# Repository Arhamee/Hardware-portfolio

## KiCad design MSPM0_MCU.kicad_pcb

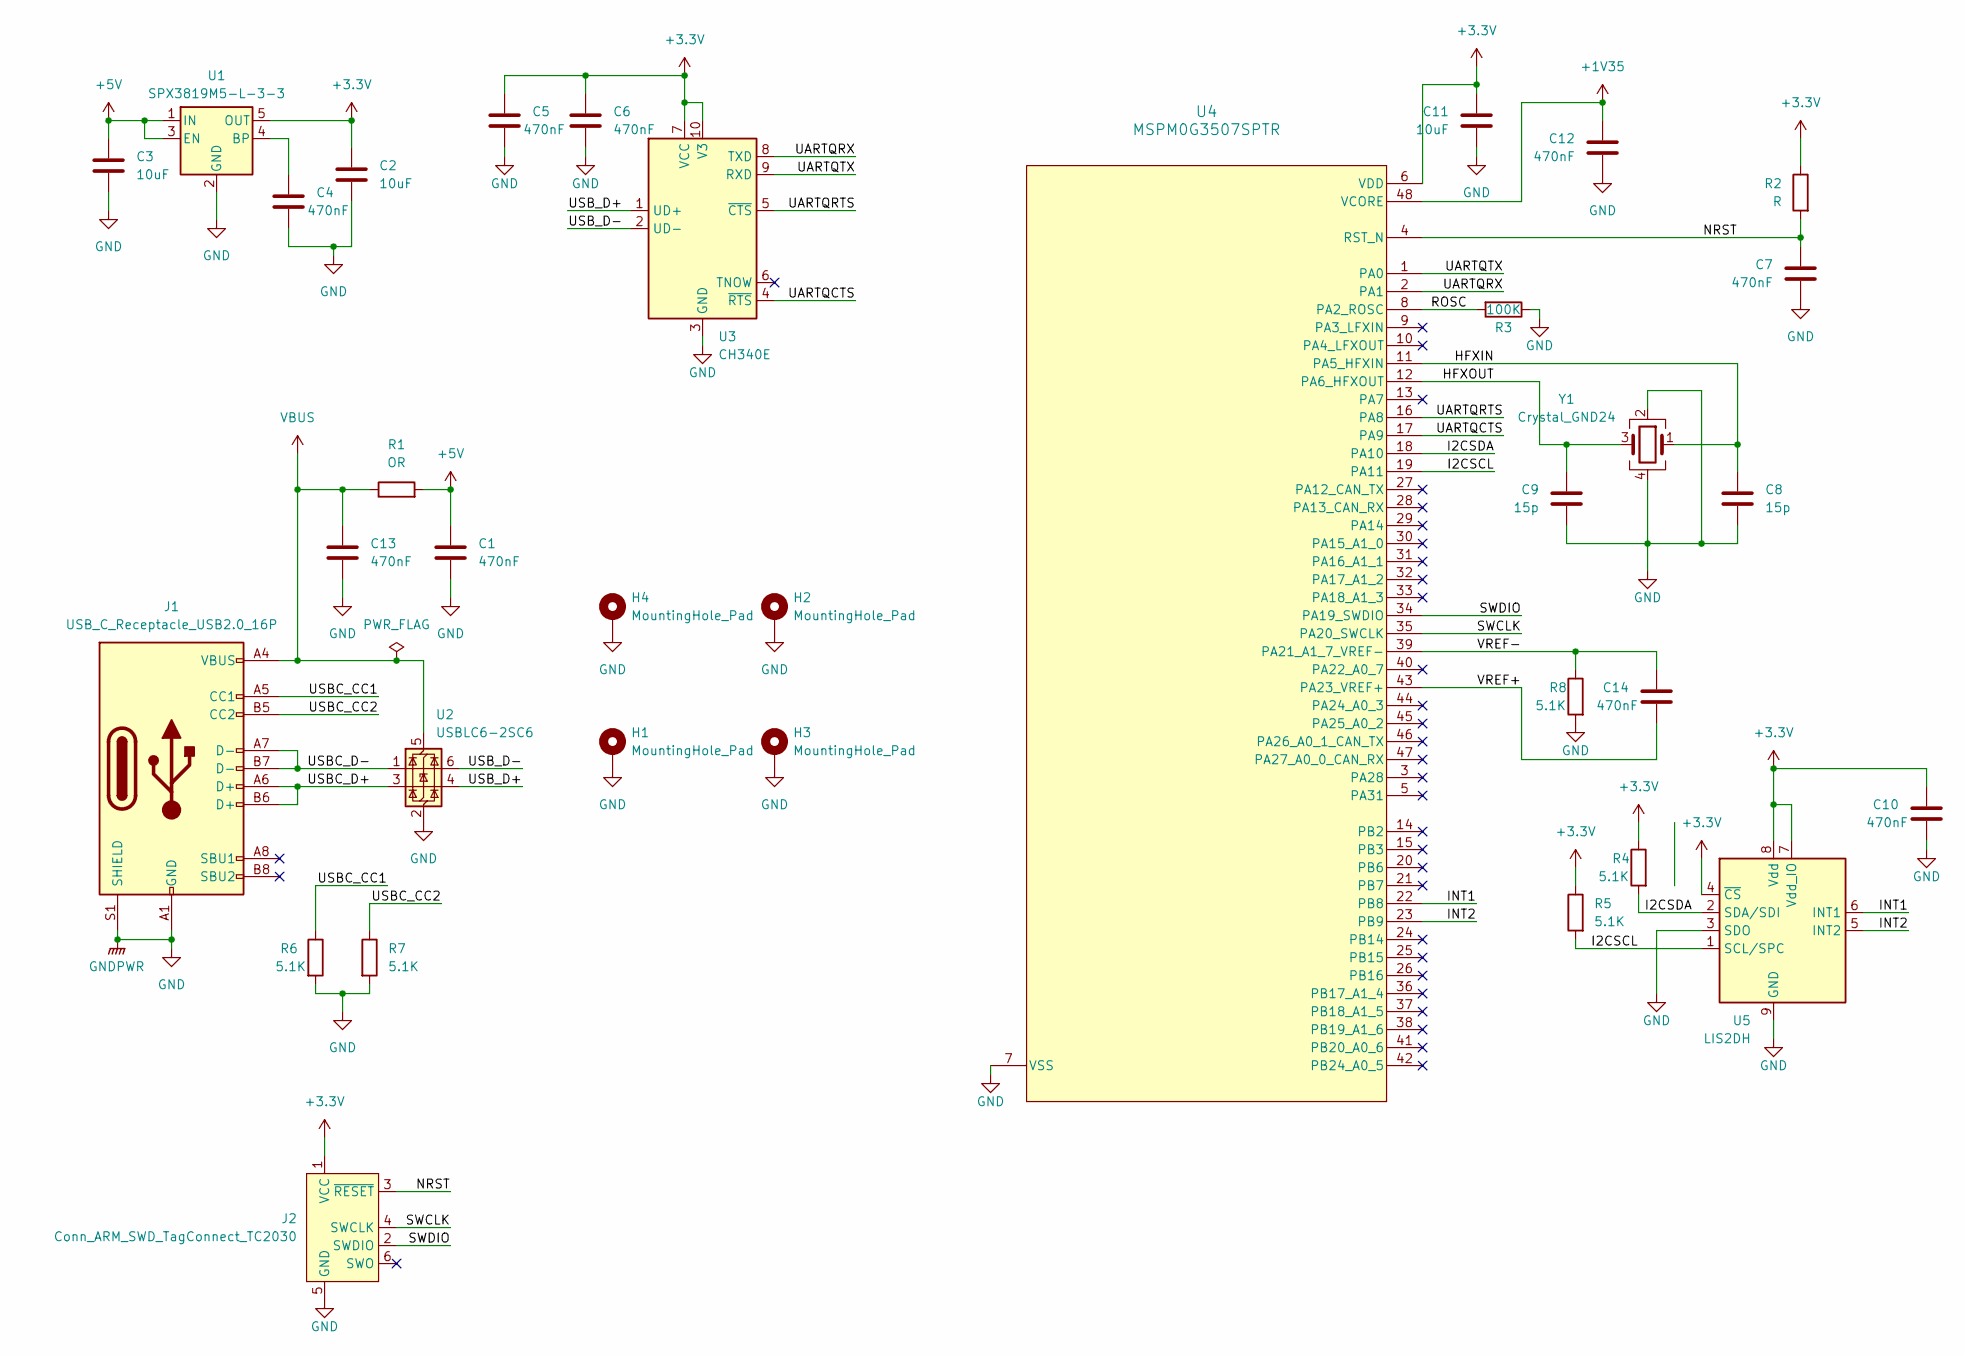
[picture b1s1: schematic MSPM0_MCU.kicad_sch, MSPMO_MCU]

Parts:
C1, C4, C5, C6, C7, C10, C12, C13, C14: 470nF; C_0603_1608Metric_Pad1.08x0.95mm_HandSolder
C2, C3, C11: 10uF; C_0805_2012Metric_Pad1.18x1.45mm_HandSolder
C8, C9: 15p; C_0603_1608Metric_Pad1.08x0.95mm_HandSolder
H1, H2, H3, H4: MountingHole_Pad; MountingHole_3.2mm_M3_Pad_Via
J1: USB_C_Receptacle_USB2.0_16P; USB_C_Receptacle_GCT_USB4105-xx-A_16P_TopMnt_Horizontal
J2: Conn_ARM_SWD_TagConnect_TC2030; Tag-Connect_TC2030-IDC-FP_2x03_P1.27mm_Vertical
R1: OR; R_0603_1608Metric_Pad0.98x0.95mm_HandSolder
R2: R; R_0603_1608Metric_Pad0.98x0.95mm_HandSolder
R3: 100K; R_0603_1608Metric_Pad0.98x0.95mm_HandSolder
R4, R5, R6, R7, R8: 5.1K; R_0603_1608Metric_Pad0.98x0.95mm_HandSolder
U1: SPX3819M5-L-3-3; SOT-23-5
U2: USBLC6-2SC6; SOT-23-6
U3: CH340E; MSOP-10_3x3mm_P0.5mm
U4: MSPM0G3507SPTR; PT0048A-IPC_A
U5: LIS2DH; LGA-14_2x2mm_P0.35mm_LayoutBorder3x4y
Y1: Crystal_GND24; Crystal_SMD_3225-4Pin_3.2x2.5mm_HandSoldering

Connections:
+1V35: C12.1, U4.48 (VCORE)
+3.3V: C2.1, C5.1, C6.1, C10.1, C11.1, J2.1 (VCC), R2.1, R4.1, R5.1, U1.5 (OUT), U3.7 (VCC), U3.10 (V3), U4.6 (VDD), U5.4 (~CS), U5.7 (Vdd_IO), U5.8 (Vdd)
+5V: C1.1, C3.1, R1.2, U1.1 (IN), U1.3 (EN)
/HFXIN: C8.1, U4.11 (PA5_HFXIN), Y1.1
/HFXOUT: C9.1, U4.12 (PA6_HFXOUT), Y1.3
/I2CSCL: R5.2, U4.19 (PA11), U5.1 (SCL/SPC)
/I2CSDA: R4.2, U4.18 (PA10), U5.2 (SDA/SDI)
/INT1: U4.22 (PB8), U5.6 (INT1)
/INT2: U4.23 (PB9), U5.5 (INT2)
/NRST: C7.1, J2.3 (~RESET), R2.2, U4.4 (RST_N)
/ROSC: R3.2, U4.8 (PA2_ROSC)
/SWCLK: J2.4 (SWCLK), U4.35 (PA20_SWCLK)
/SWDIO: J2.2 (SWDIO), U4.34 (PA19_SWDIO)
/UARTQCTS: U3.4 (~RTS), U4.17 (PA9)
/UARTQRTS: U3.5 (~CTS), U4.16 (PA8)
/UARTQRX: U3.8 (TXD), U4.2 (PA1)
/UARTQTX: U3.9 (RXD), U4.1 (PA0)
/USBC_CC1: J1.A5 (CC1), R6.1
/USBC_CC2: J1.B5 (CC2), R7.1
/USBC_D+: J1.A6 (D+), J1.B6 (D+), U2.3 (I/O2)
/USBC_D-: J1.A7 (D-), J1.B7 (D-), U2.1 (I/O1)
/USB_D+: U2.4 (I/O2), U3.1 (UD+)
/USB_D-: U2.6 (I/O1), U3.2 (UD-)
/VREF+: C14.2, U4.43 (PA23_VREF+)
/VREF-: C14.1, R8.1, U4.39 (PA21_A1_7_VREF-)
GND: C1.2, C2.2, C3.2, C4.2, C5.2, C6.2, C7.2, C8.2, C9.2, C10.2, C11.2, C12.2, C13.2, H1.1, H2.1, H3.1, H4.1, J1.A1 (GND), J1.A12 (GND), J1.B1 (GND), J1.B12 (GND), J1.S1 (SHIELD), J2.5 (GND), R3.1, R6.2, R7.2, R8.2, U1.2 (GND), U2.2 (GND), U3.3 (GND), U4.7 (VSS), U5.3 (SDO), U5.9 (GND), U5.10 (GND), U5.11 (GND), U5.12 (GND), U5.13 (GND), U5.14 (GND), Y1.2, Y1.4
unnamed: C4.1, U1.4 (BP)
VBUS: C13.1, J1.A4 (VBUS), J1.A9 (VBUS), J1.B4 (VBUS), J1.B9 (VBUS), R1.1, U2.5 (VBUS)

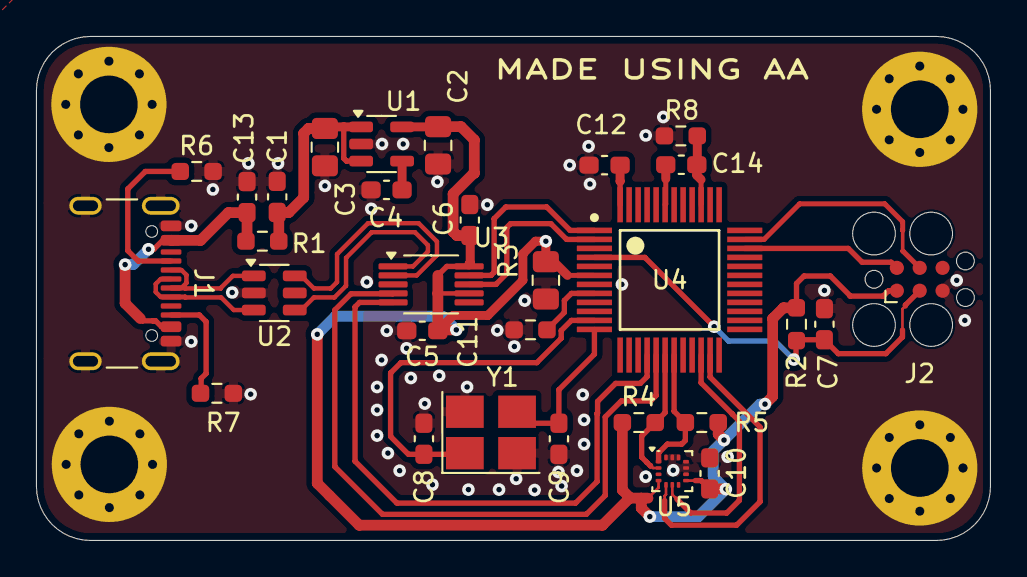
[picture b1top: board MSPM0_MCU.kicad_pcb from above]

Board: 2 copper layers, 53.0 x 28.0 mm, 34 parts (0 on the bottom side), 28 nets.

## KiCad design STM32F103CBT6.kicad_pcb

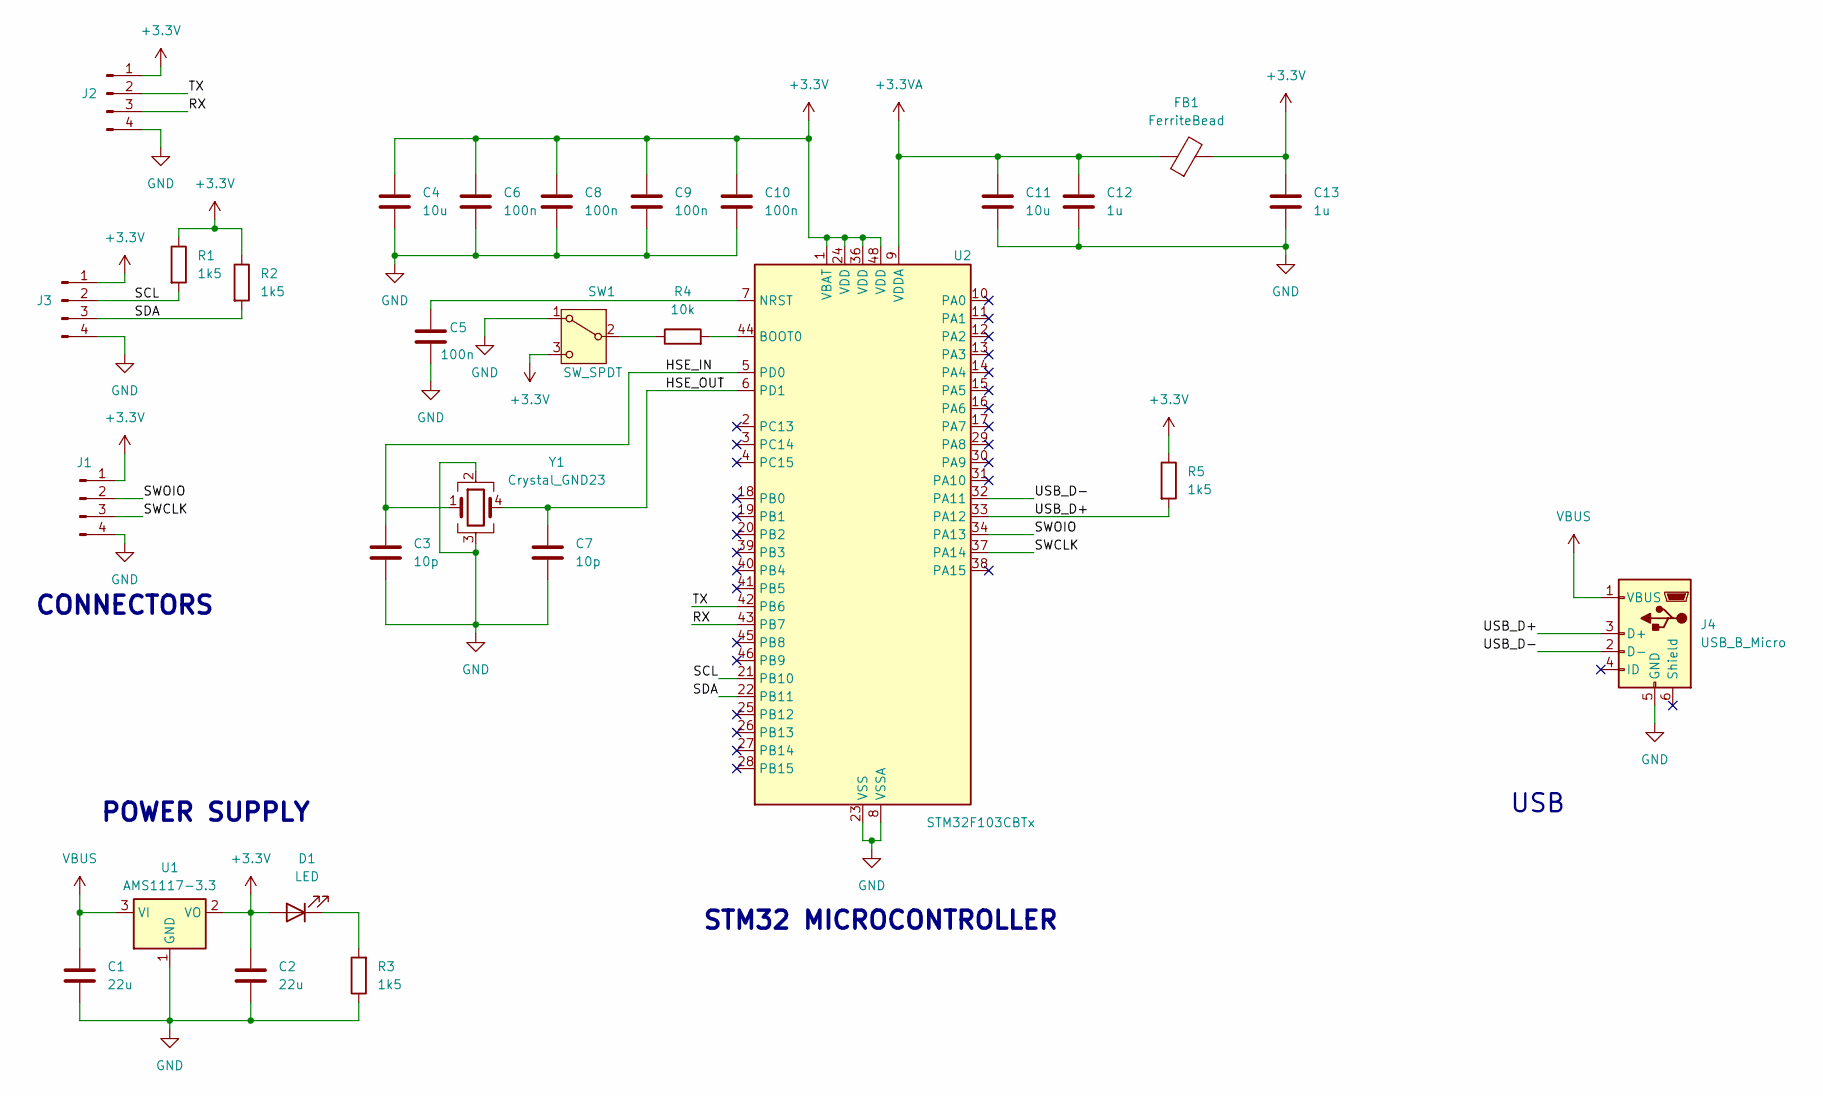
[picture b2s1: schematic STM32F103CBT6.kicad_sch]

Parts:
C1, C2: 22u; C_0805_2012Metric_Pad1.18x1.45mm_HandSolder
C3, C7: 10p; C_0402_1005Metric_Pad0.74x0.62mm_HandSolder
C4: 10u; C_0402_1005Metric_Pad0.74x0.62mm_HandSolder
C5, C6, C8, C9, C10: 100n; C_0402_1005Metric_Pad0.74x0.62mm_HandSolder
C11: 10u; C_0603_1608Metric_Pad1.08x0.95mm_HandSolder
C12, C13: 1u; C_0402_1005Metric_Pad0.74x0.62mm_HandSolder
D1: LED; LED_0201_0603Metric_Pad0.64x0.40mm_HandSolder
FB1: FerriteBead; L_0201_0603Metric_Pad0.64x0.40mm_HandSolder
J1, J2, J3: Conn_01x04_Pin; PinHeader_1x04_P2.54mm_Vertical
J4: USB_B_Micro; USB_Micro-B_Wuerth_629105150521
R1, R2, R3, R5: 1k5; R_0402_1005Metric_Pad0.72x0.64mm_HandSolder
R4: 10k; R_0402_1005Metric_Pad0.72x0.64mm_HandSolder
SW1: SW_SPDT; SW_Slide-03_Wuerth-WS-SLTV_10x2.5x6.4_P2.54mm
U1: AMS1117-3.3; SOT-223-3_TabPin2
U2: STM32F103CBTx; LQFP-48_7x7mm_P0.5mm
Y1: Crystal_GND23; Crystal_SMD_3225-4Pin_3.2x2.5mm

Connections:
+3.3V: C2.1, C4.1, C6.1, C8.1, C9.1, C10.1, C13.1, D1.2 (A), FB1.2, J1.1, J2.1, J3.1, R1.1, R2.1, R5.1, SW1.3 (C), U1.2 (VO), U2.1 (VBAT), U2.24 (VDD), U2.36 (VDD), U2.48 (VDD)
+3.3VA: C11.1, C12.1, FB1.1, U2.9 (VDDA)
/HSE_IN: C3.1, U2.5 (PD0), Y1.1
/HSE_OUT: C7.1, U2.6 (PD1), Y1.4
/RX: J2.3, U2.43 (PB7)
/SCL: J3.2, R1.2, U2.21 (PB10)
/SDA: J3.3, R2.2, U2.22 (PB11)
/SWCLK: J1.3, U2.37 (PA14)
/SWOIO: J1.2, U2.34 (PA13)
/TX: J2.2, U2.42 (PB6)
/USB_D+: J4.3 (D+), R5.2, U2.33 (PA12)
/USB_D-: J4.2 (D-), U2.32 (PA11)
GND: C1.2, C2.2, C3.2, C4.2, C5.2, C6.2, C7.2, C8.2, C9.2, C10.2, C11.2, C12.2, C13.2, J1.4, J2.4, J3.4, J4.5 (GND), R3.1, SW1.1 (A), U1.1 (GND), U2.8 (VSSA), U2.23 (VSS), U2.35 (VSS), U2.47 (VSS), Y1.2, Y1.3
unnamed: D1.1 (K), R3.2
unnamed: R4.1, SW1.2 (B)
unnamed: R4.2, U2.44 (BOOT0)
unnamed: C5.1, U2.7 (NRST)
VBUS: C1.1, J4.1 (VBUS), U1.3 (VI)

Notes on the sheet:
POWER SUPPLY
STM32 MICROCONTROLLER
CONNECTORS
USB

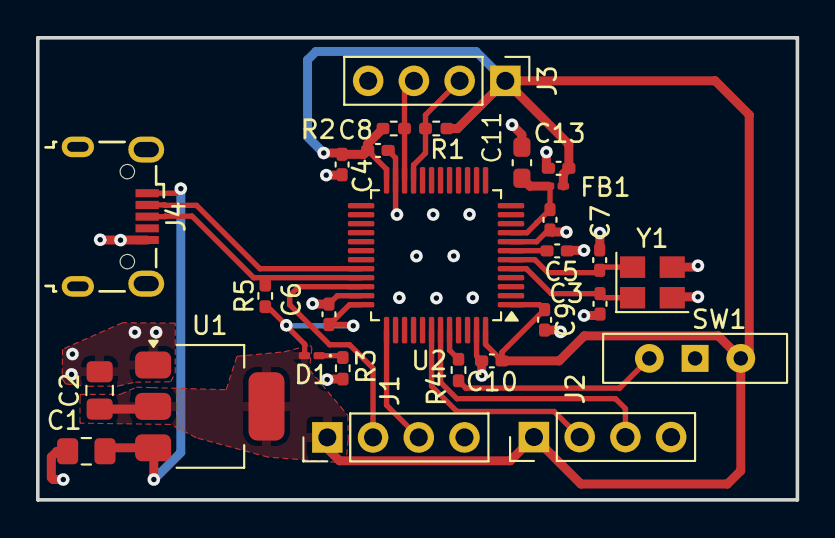
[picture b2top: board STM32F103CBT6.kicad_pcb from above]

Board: 2 copper layers, 42.2 x 25.7 mm, 28 parts (0 on the bottom side), 18 nets.

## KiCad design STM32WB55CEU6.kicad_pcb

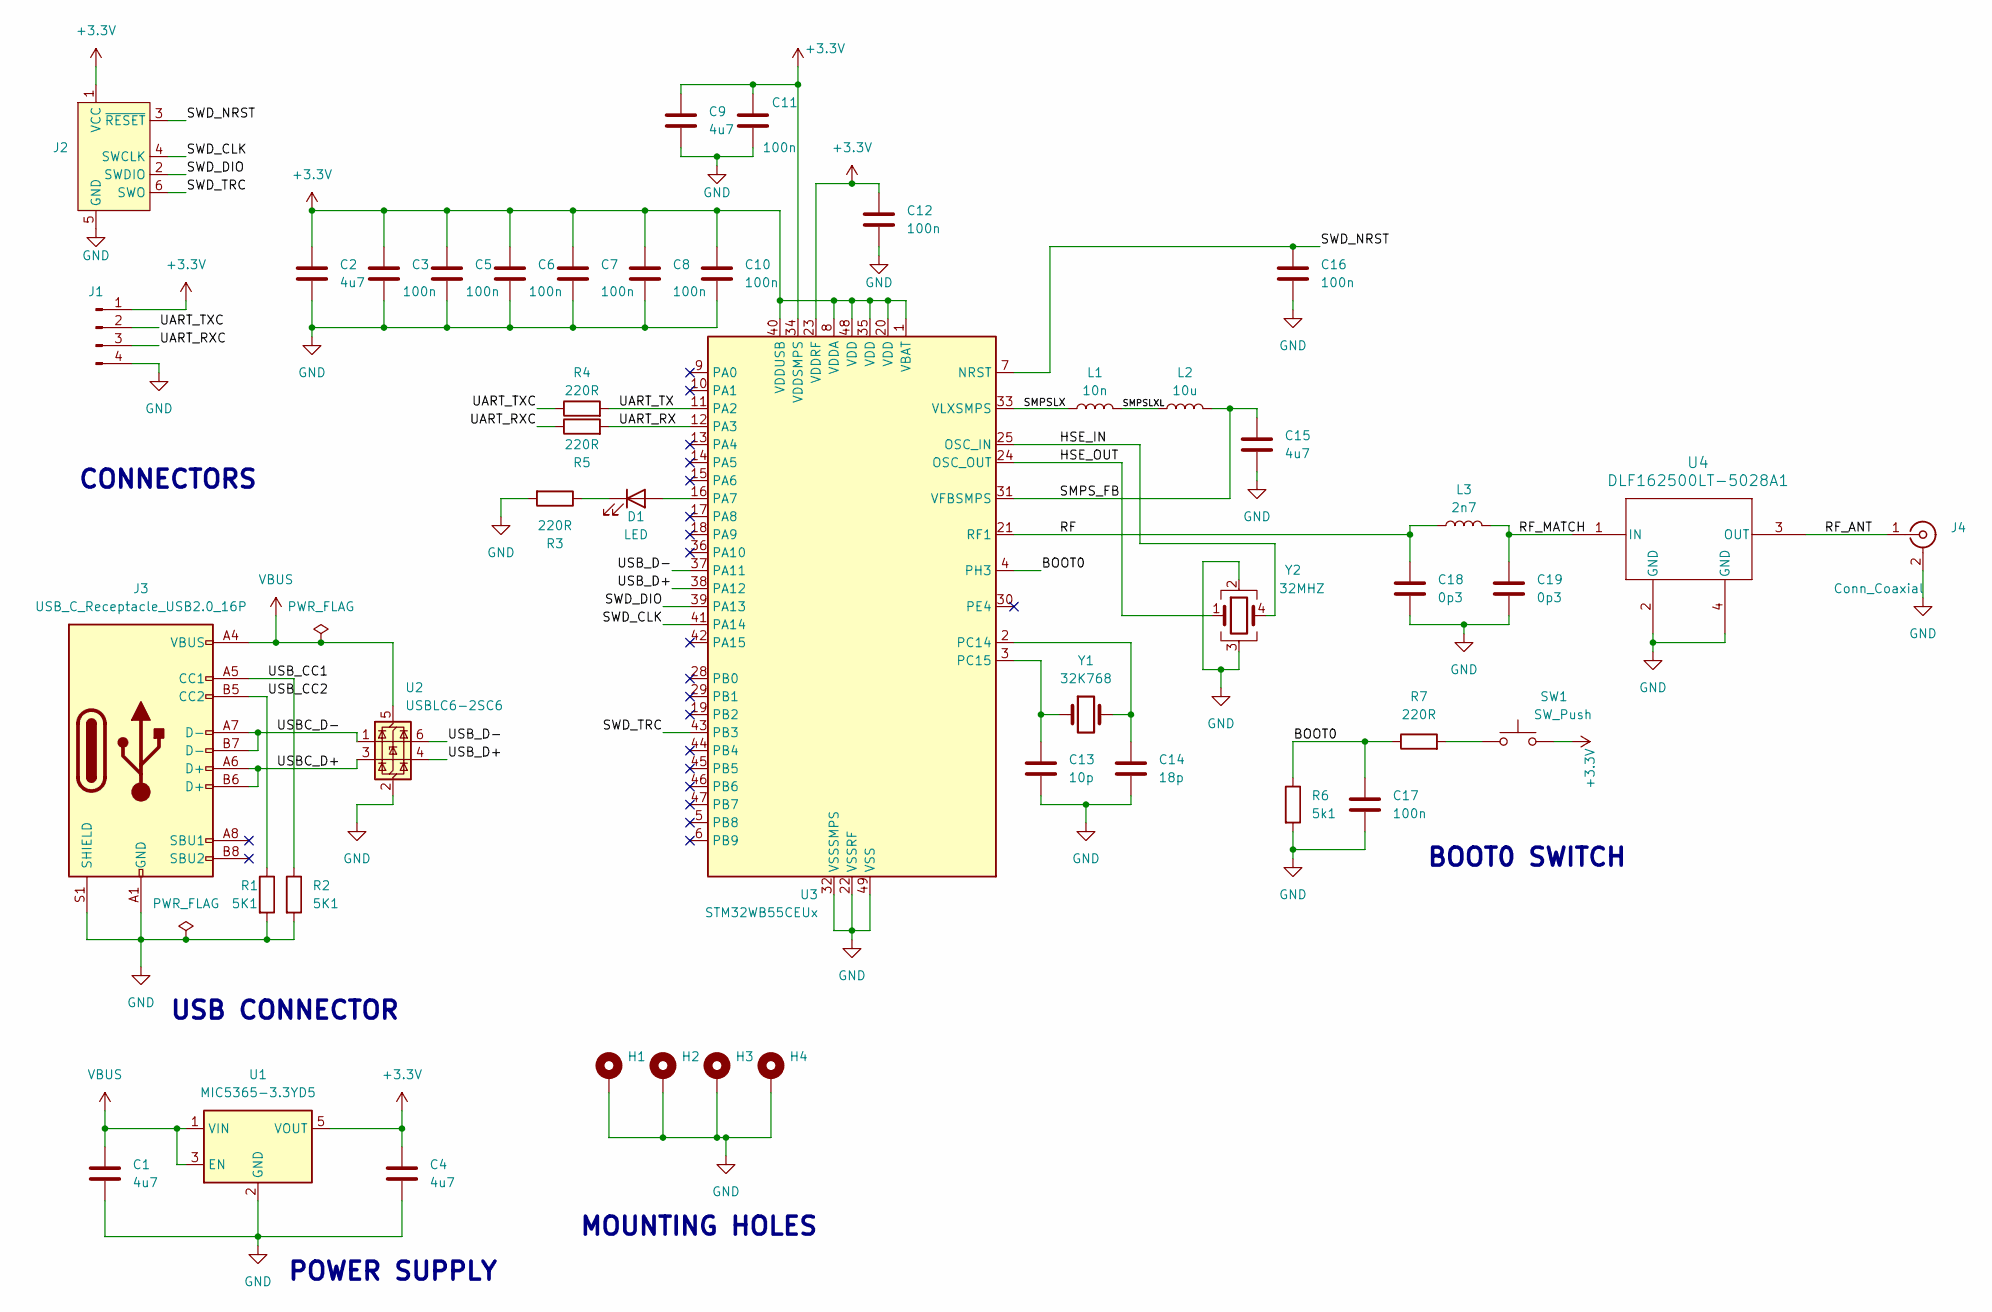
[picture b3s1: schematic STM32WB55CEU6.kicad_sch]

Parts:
C1, C2, C4, C9, C15: 4u7; C_0603_1608Metric_Pad1.08x0.95mm_HandSolder
C3, C5, C6, C7, C8, C10, C11, C12, C16, C17: 100n; C_0402_1005Metric_Pad0.74x0.62mm_HandSolder
C13: 10p; C_0402_1005Metric_Pad0.74x0.62mm_HandSolder
C14: 18p; C_0402_1005Metric_Pad0.74x0.62mm_HandSolder
C18, C19: 0p3; C_0402_1005Metric_Pad0.74x0.62mm_HandSolder
D1: LED; LED_0402_1005Metric_Pad0.77x0.64mm_HandSolder
H1, H2, H3, H4: MountingHole_Pad; MountingHole_2.2mm_M2_Pad
J1: Conn_01x04_Pin; Molex_PicoBlade_53048-0410_1x04_P1.25mm_Horizontal
J2: Conn_ARM_SWD_TagConnect_TC2030; Tag-Connect_TC2030-IDC-FP_2x03_P1.27mm_Vertical
J3: USB_C_Receptacle_USB2.0_16P; USB_C_Receptacle_GCT_USB4105-xx-A_16P_TopMnt_Horizontal
J4: Conn_Coaxial; U.FL_Hirose_U.FL-R-SMT-1_Vertical
L1: 10n; L_0402_1005Metric_Pad0.77x0.64mm_HandSolder
L2: 10u; L_0805_2012Metric_Pad1.05x1.20mm_HandSolder
L3: 2n7; L_0402_1005Metric_Pad0.77x0.64mm_HandSolder
R1, R2: 5K1; R_0402_1005Metric_Pad0.72x0.64mm_HandSolder
R3, R4, R5, R7: 220R; R_0402_1005Metric_Pad0.72x0.64mm_HandSolder
R6: 5k1; R_0402_1005Metric_Pad0.72x0.64mm_HandSolder
SW1: SW_Push; SW_SPST_CK_RS282G05A3
U1: MIC5365-3.3YD5; SOT-23-5
U2: USBLC6-2SC6; SOT-23-6
U3: STM32WB55CEUx; QFN-48-1EP_7x7mm_P0.5mm_EP5.6x5.6mm
U4: DLF162500LT-5028A1; DLF-4_1P6X0P8
Y1: 32K768; Crystal_SMD_2012-2Pin_2.0x1.2mm
Y2: 32MHZ; Crystal_SMD_2016-4Pin_2.0x1.6mm

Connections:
+3.3V: C2.1, C3.1, C4.1, C5.1, C6.1, C7.1, C8.1, C9.1, C10.1, C11.1, C12.1, J1.1, J2.1 (VCC), SW1.2, U1.5 (VOUT), U3.1 (VBAT), U3.8 (VDDA), U3.20 (VDD), U3.23 (VDDRF), U3.34 (VDDSMPS), U3.35 (VDD), U3.40 (VDDUSB), U3.48 (VDD)
/BOOT0: C17.1, R6.1, R7.1, U3.4 (PH3)
/HSE_IN: U3.25 (OSC_IN), Y2.4
/HSE_OUT: U3.24 (OSC_OUT), Y2.1
/RF: C18.1, L3.1, U3.21 (RF1)
/RF_ANT: J4.1 (In), U4.3 (OUT)
/RF_MATCH: C19.1, L3.2, U4.1 (IN)
/SMPSLX: L1.1, U3.33 (VLXSMPS)
/SMPSLXL: L1.2, L2.1
/SMPS_FB: C15.1, L2.2, U3.31 (VFBSMPS)
/SWD_CLK: J2.4 (SWCLK), U3.41 (PA14)
/SWD_DIO: J2.2 (SWDIO), U3.39 (PA13)
/SWD_NRST: C16.1, J2.3 (~RESET), U3.7 (NRST)
/SWD_TRC: J2.6 (SWO), U3.43 (PB3)
/UART_RX: R5.2, U3.12 (PA3)
/UART_RXC: J1.3, R5.1
/UART_TX: R4.2, U3.11 (PA2)
/UART_TXC: J1.2, R4.1
/USBC_D+: J3.A6 (D+), J3.B6 (D+), U2.3 (I/O2)
/USBC_D-: J3.A7 (D-), J3.B7 (D-), U2.1 (I/O1)
/USB_CC1: J3.A5 (CC1), R2.1
/USB_CC2: J3.B5 (CC2), R1.1
/USB_D+: U2.4 (I/O2), U3.38 (PA12)
/USB_D-: U2.6 (I/O1), U3.37 (PA11)
GND: C1.2, C2.2, C3.2, C4.2, C5.2, C6.2, C7.2, C8.2, C9.2, C10.2, C11.2, C12.2, C13.2, C14.2, C15.2, C16.2, C17.2, C18.2, C19.2, H1.1, H2.1, H3.1, H4.1, J1.4, J2.5 (GND), J3.A1 (GND), J3.A12 (GND), J3.B1 (GND), J3.B12 (GND), J3.S1 (SHIELD), J4.2 (Ext), R1.2, R2.2, R3.2, R6.2, U1.2 (GND), U2.2 (GND), U3.22 (VSSRF), U3.32 (VSSSMPS), U3.49 (VSS), U4.2 (GND), U4.4 (GND), Y2.2, Y2.3
unnamed: D1.2 (A), U3.16 (PA7)
unnamed: D1.1 (K), R3.1
unnamed: R7.2, SW1.1
unnamed: C14.1, U3.2 (PC14), Y1.2
unnamed: C13.1, U3.3 (PC15), Y1.1
VBUS: C1.1, J3.A4 (VBUS), J3.A9 (VBUS), J3.B4 (VBUS), J3.B9 (VBUS), U1.1 (VIN), U1.3 (EN), U2.5 (VBUS)

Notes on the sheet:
POWER SUPPLY
USB CONNECTOR
BOOT0 SWITCH
CONNECTORS
MOUNTING HOLES

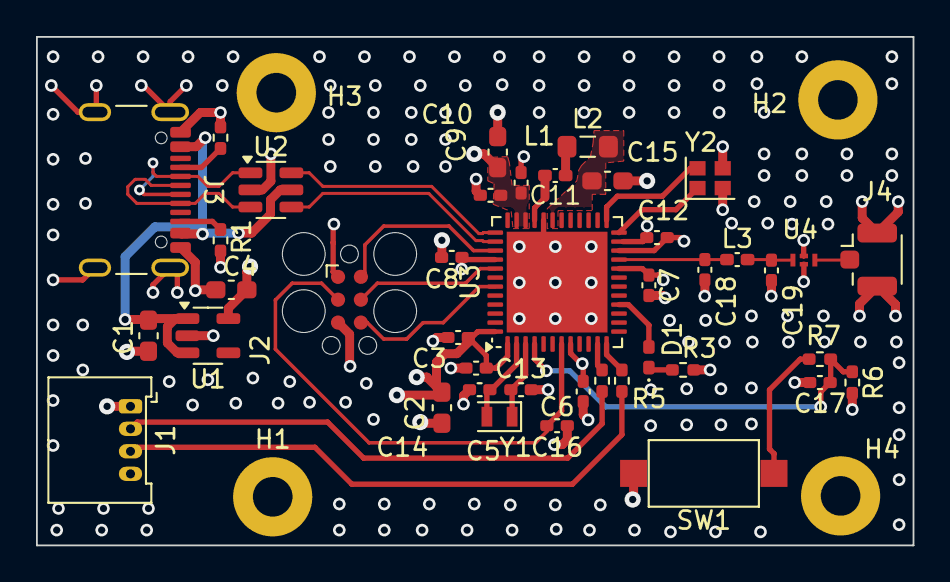
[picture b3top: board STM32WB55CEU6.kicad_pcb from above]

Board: 4 copper layers, 48.7 x 28.2 mm, 45 parts (0 on the bottom side), 31 nets.

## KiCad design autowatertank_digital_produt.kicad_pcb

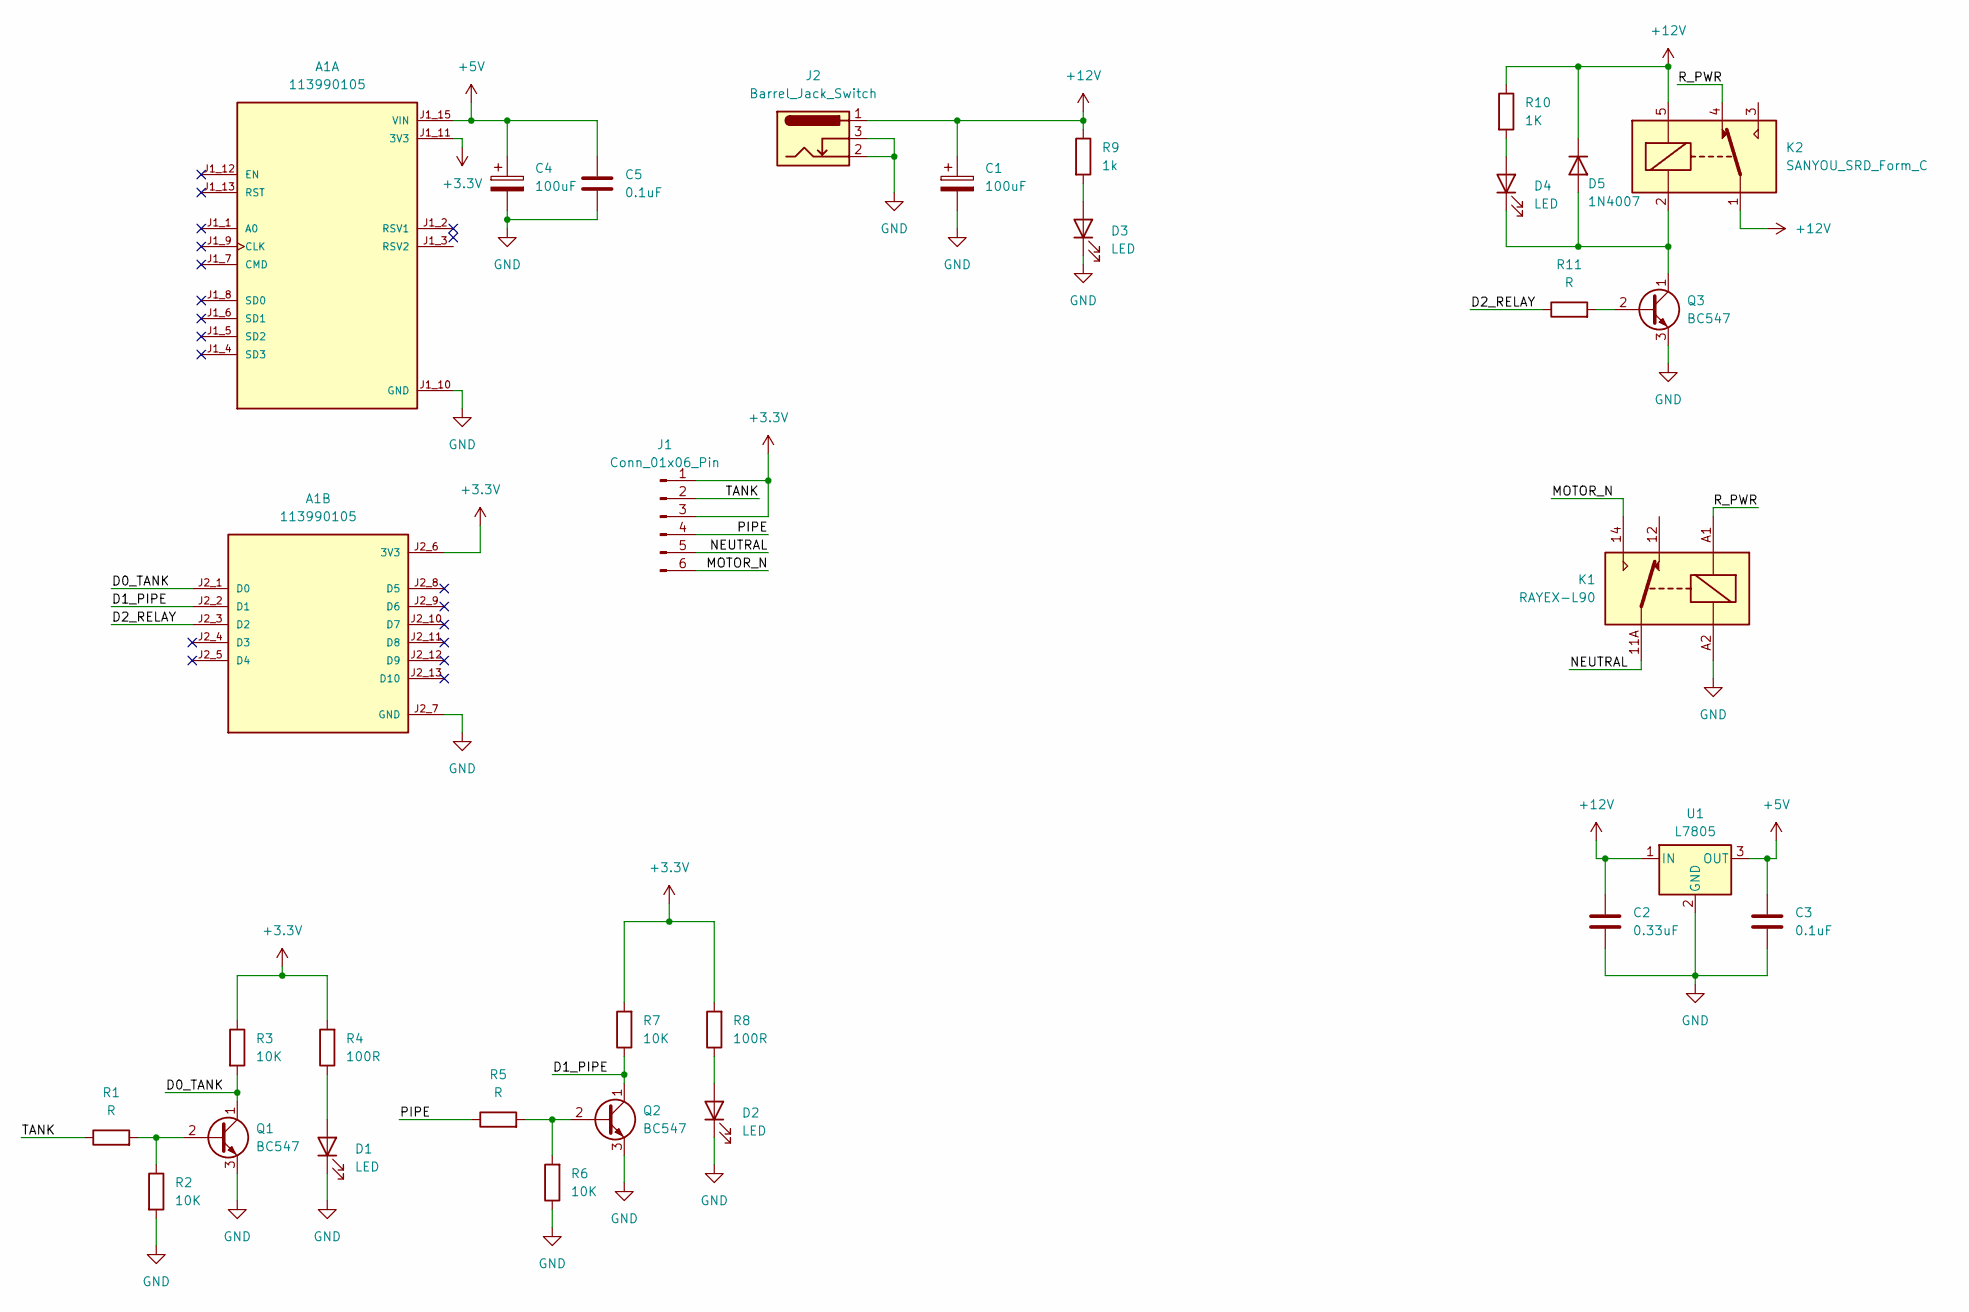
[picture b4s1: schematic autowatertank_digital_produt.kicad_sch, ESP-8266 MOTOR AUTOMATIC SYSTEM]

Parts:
A1: 113990105; SEEED_113990105; PARTREV N/A
C1, C4: 100uF; CP_Radial_D6.3mm_P2.50mm
C2: 0.33uF; C_Disc_D4.7mm_W2.5mm_P5.00mm
C3, C5: 0.1uF; C_Disc_D4.7mm_W2.5mm_P5.00mm
D1, D2, D3, D4: LED; LED_D5.0mm
D5: 1N4007; D_DO-41_SOD81_P10.16mm_Horizontal
J1: Conn_01x06_Pin; TE_2-1437667-9
J2: Barrel_Jack_Switch; BarrelJack_Horizontal
K1: RAYEX-L90; Relay_SPDT_RAYEX-L90
K2: SANYOU_SRD_Form_C; Relay_SPDT_SANYOU_SRD_Series_Form_C
Q1, Q2, Q3: BC547; TO-92_Inline
R1, R5, R11: R; R_Axial_DIN0207_L6.3mm_D2.5mm_P10.16mm_Horizontal
R2, R3, R6, R7: 10K; R_Axial_DIN0207_L6.3mm_D2.5mm_P10.16mm_Horizontal
R4, R8: 100R; R_Axial_DIN0207_L6.3mm_D2.5mm_P10.16mm_Horizontal
R9: 1k; R_Axial_DIN0207_L6.3mm_D2.5mm_P10.16mm_Horizontal
R10: 1K; R_Axial_DIN0207_L6.3mm_D2.5mm_P10.16mm_Horizontal
U1: L7805; TO-220-3_Vertical

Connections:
+3.3V: A1.J1_11 (3V3), A1.J2_6 (3V3), A1.J2_15 (3V3), J1.1, J1.3, R3.1, R4.2, R7.2, R8.2
+5V: A1.J1_15 (VIN), C3.1, C4.1, C5.1, U1.3 (OUT)
+12V: C1.1, C2.1, D5.1 (K), J2.1, K2.1, K2.5, R9.1, R10.1, U1.1 (IN)
/D0_TANK: A1.J2_1 (D0), Q1.1 (C), R3.2
/D1_PIPE: A1.J2_2 (D1), Q2.1 (C), R7.1
/D2_RELAY: A1.J2_3 (D2), R11.1
/MOTOR_N: J1.6, K1.14
/NEUTRAL: J1.5, K1.11A, K1.11B
/PIPE: J1.4, R5.1
/R_PWR: K1.A1, K2.4
/TANK: J1.2, R1.1
GND: A1.J1_10 (GND), A1.J1_14 (GND), A1.J2_7 (GND), A1.J2_14 (GND), C1.2, C2.2, C3.2, C4.2, C5.2, D1.1 (K), D2.1 (K), D3.1 (K), J2.2, J2.3, K1.A2, Q1.3 (E), Q2.3 (E), Q3.3 (E), R2.2, R6.1, U1.2 (GND)
unnamed: D1.2 (A), R4.1
unnamed: D2.2 (A), R8.1
unnamed: D3.2 (A), R9.2
unnamed: D4.2 (A), R10.2
unnamed: D4.1 (K), D5.2 (A), K2.2, Q3.1 (C)
unnamed: Q1.2 (B), R1.2, R2.1
unnamed: Q2.2 (B), R5.2, R6.2
unnamed: Q3.2 (B), R11.2

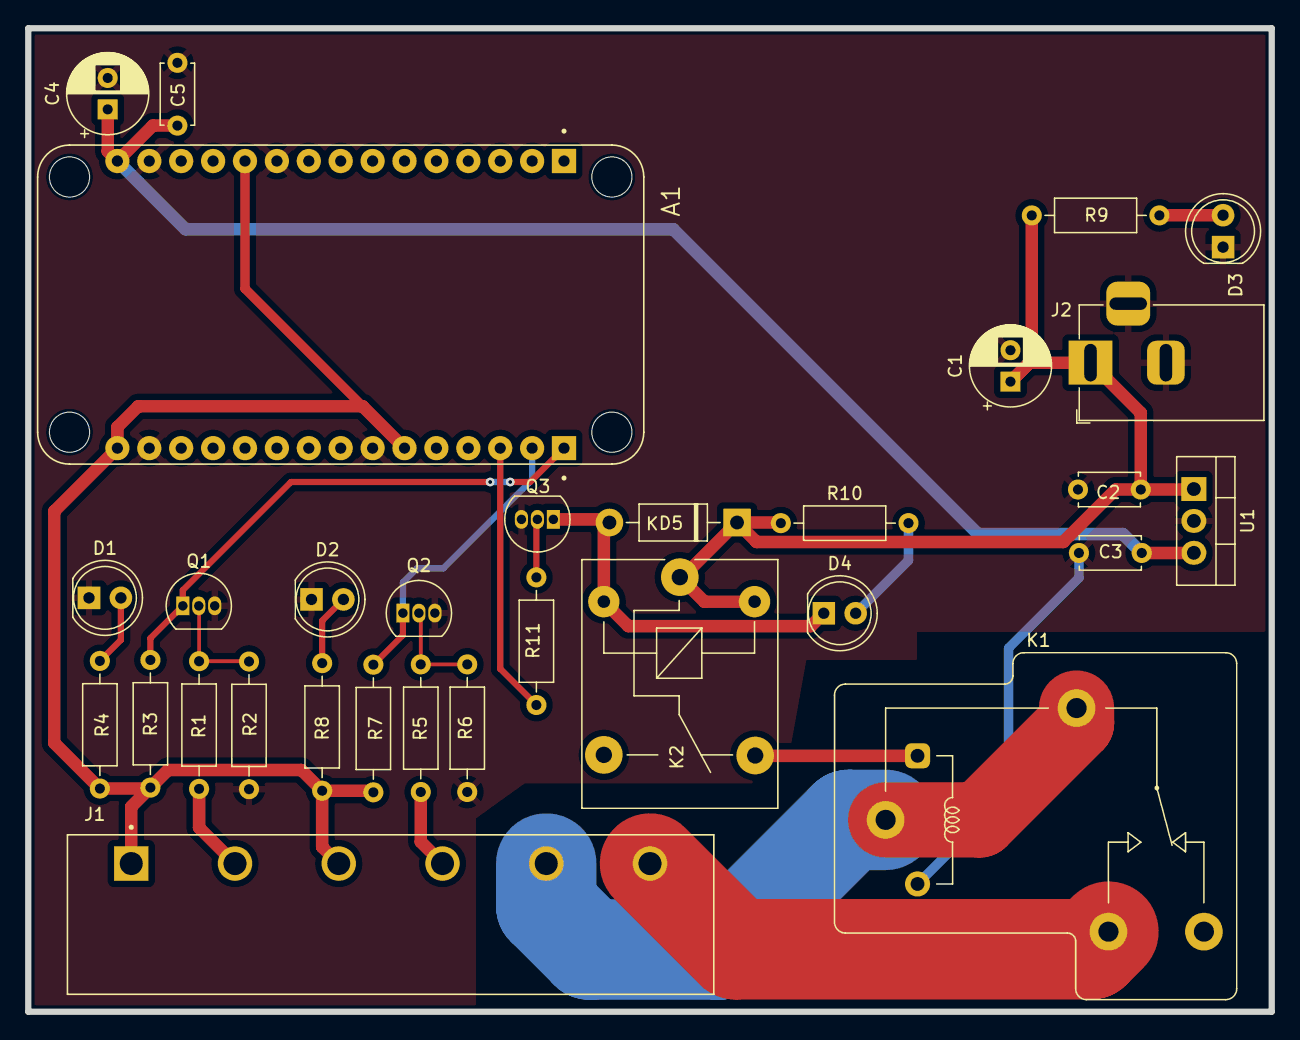
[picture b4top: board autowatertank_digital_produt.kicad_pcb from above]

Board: 2 copper layers, 99.0 x 78.3 mm, 30 parts (0 on the bottom side), 20 nets.

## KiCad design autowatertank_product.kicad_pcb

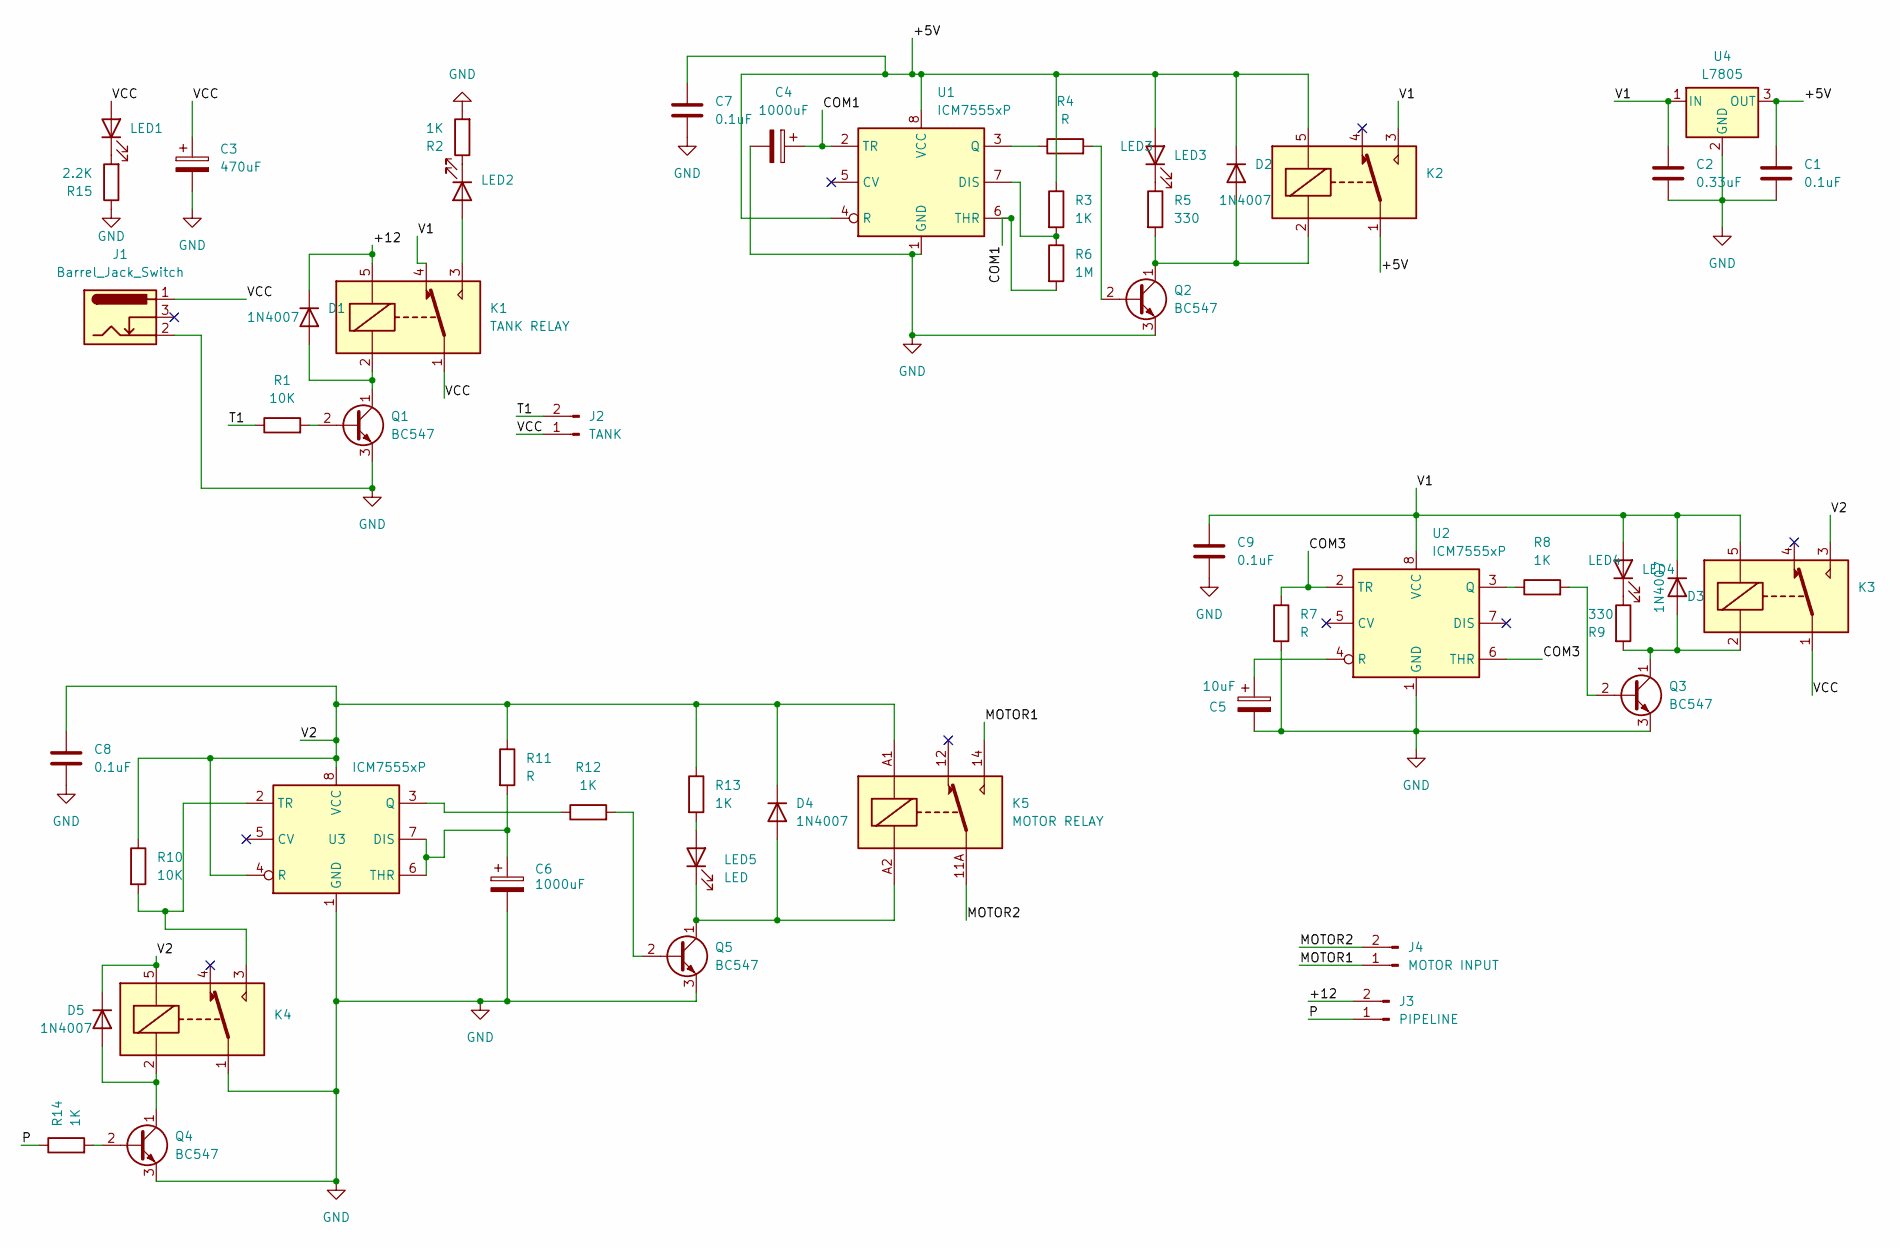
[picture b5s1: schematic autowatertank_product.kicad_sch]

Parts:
C1, C7, C8, C9: 0.1uF; C_Disc_D3.0mm_W2.0mm_P2.50mm
C2: 0.33uF; C_Disc_D3.0mm_W2.0mm_P2.50mm
C3: 470uF; CP_Radial_D8.0mm_P3.50mm
C4, C6: 1000uF; CP_Radial_D8.0mm_P5.00mm
C5: 10uF; CP_Radial_D4.0mm_P2.00mm
D1, D2, D3, D4, D5: 1N4007; D_DO-41_SOD81_P10.16mm_Horizontal
J1: Barrel_Jack_Switch; BarrelJack_GCT_DCJ200-10-A_Horizontal
J2: TANK; TerminalBlock_MaiXu_MX126-5.0-02P_1x02_P5.00mm
J3: PIPELINE; TerminalBlock_MaiXu_MX126-5.0-02P_1x02_P5.00mm
J4: MOTOR INPUT; TerminalBlock_MaiXu_MX126-5.0-02P_1x02_P5.00mm
K1: TANK RELAY; Relay_SPDT_SANYOU_SRD_Series_Form_C
K2: 555 IC RELAY 1; Relay_SPDT_SANYOU_SRD_Series_Form_C
K3, K4: Relay_SPDT_SANYOU_SRD_Series_Form_C
K5: MOTOR RELAY; Relay_SPDT_RAYEX-L90
LED1: LED_D5.0mm_Clear
LED2: FULL; LED_D5.0mm_Clear
LED3: LED3; LED_D5.0mm_Clear
LED4: LED4; LED_D5.0mm_Clear
LED5: LED; LED_D5.0mm_Clear
Q1, Q2, Q3, Q4, Q5: BC547; TO-92_Inline
R1, R10: 10K; R_Axial_DIN0207_L6.3mm_D2.5mm_P10.16mm_Horizontal
R2, R3, R8, R12, R13, R14: 1K; R_Axial_DIN0207_L6.3mm_D2.5mm_P10.16mm_Horizontal
R4, R7, R11: R; R_Axial_DIN0207_L6.3mm_D2.5mm_P10.16mm_Horizontal
R5, R9: 330; R_Axial_DIN0207_L6.3mm_D2.5mm_P10.16mm_Horizontal
R6: 1M; R_Axial_DIN0207_L6.3mm_D2.5mm_P10.16mm_Horizontal
R15: 2.2K; R_Axial_DIN0207_L6.3mm_D2.5mm_P10.16mm_Horizontal
U1, U2, U3: ICM7555xP; DIP-8_W7.62mm
U4: L7805; TO-220-3_Vertical

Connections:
/+5V: C1.1, C7.1, D2.1 (K), K2.1, K2.5, LED3.2 (A), R3.1, U1.4 (R), U1.8 (VCC), U4.3 (OUT)
/+12: D1.1 (K), J3.2, K1.5
/COM1: C4.1, R6.2, U1.2 (TR), U1.6 (THR)
/COM3: R7.1, U2.2 (TR), U2.6 (THR)
/MOTOR1: J4.1, K5.14
/MOTOR2: J4.2, K5.11A, K5.11B
/P: J3.1, R14.1
/T1: J2.2, R1.1
/V1: C2.1, C9.1, D3.1 (K), K1.4, K2.3, K3.5, LED4.2 (A), U2.8 (VCC), U4.1 (IN)
/V2: C8.1, D4.1 (K), D5.1 (K), K3.3, K4.5, K5.A1, R10.1, R11.1, R13.1, U3.4 (R), U3.8 (VCC)
/VCC: C3.1, J1.1, J2.1, K1.1, K3.1, LED1.2 (A)
GND: C1.2, C2.2, C3.2, C4.2, C5.2, C6.2, C7.2, C8.2, C9.2, J1.2, K4.1, Q1.3 (E), Q2.3 (E), Q3.3 (E), Q4.3 (E), Q5.3 (E), R2.2, R7.2, R15.1, U1.1 (GND), U2.1 (GND), U3.1 (GND), U4.2 (GND)
unnamed: D1.2 (A), K1.2, Q1.1 (C)
unnamed: D2.2 (A), K2.2, Q2.1 (C), R5.2
unnamed: D3.2 (A), K3.2, Q3.1 (C), R9.2
unnamed: D4.2 (A), K5.A2, LED5.1 (K), Q5.1 (C)
unnamed: D5.2 (A), K4.2, Q4.1 (C)
unnamed: LED1.1 (K), R15.2
unnamed: K1.3, LED2.2 (A)
unnamed: LED2.1 (K), R2.1
unnamed: LED3.1 (K), R5.1
unnamed: LED4.1 (K), R9.1
unnamed: LED5.2 (A), R13.2
unnamed: Q1.2 (B), R1.2
unnamed: Q2.2 (B), R4.2
unnamed: Q3.2 (B), R8.2
unnamed: Q4.2 (B), R14.2
unnamed: Q5.2 (B), R12.2
unnamed: R3.2, R6.1, U1.7 (DIS)
unnamed: R4.1, U1.3 (Q)
unnamed: R8.1, U2.3 (Q)
unnamed: C5.1, U2.4 (R)
unnamed: C6.1, R11.2, U3.6 (THR), U3.7 (DIS)
unnamed: R12.1, U3.3 (Q)
unnamed: K4.3, R10.2, U3.2 (TR)
